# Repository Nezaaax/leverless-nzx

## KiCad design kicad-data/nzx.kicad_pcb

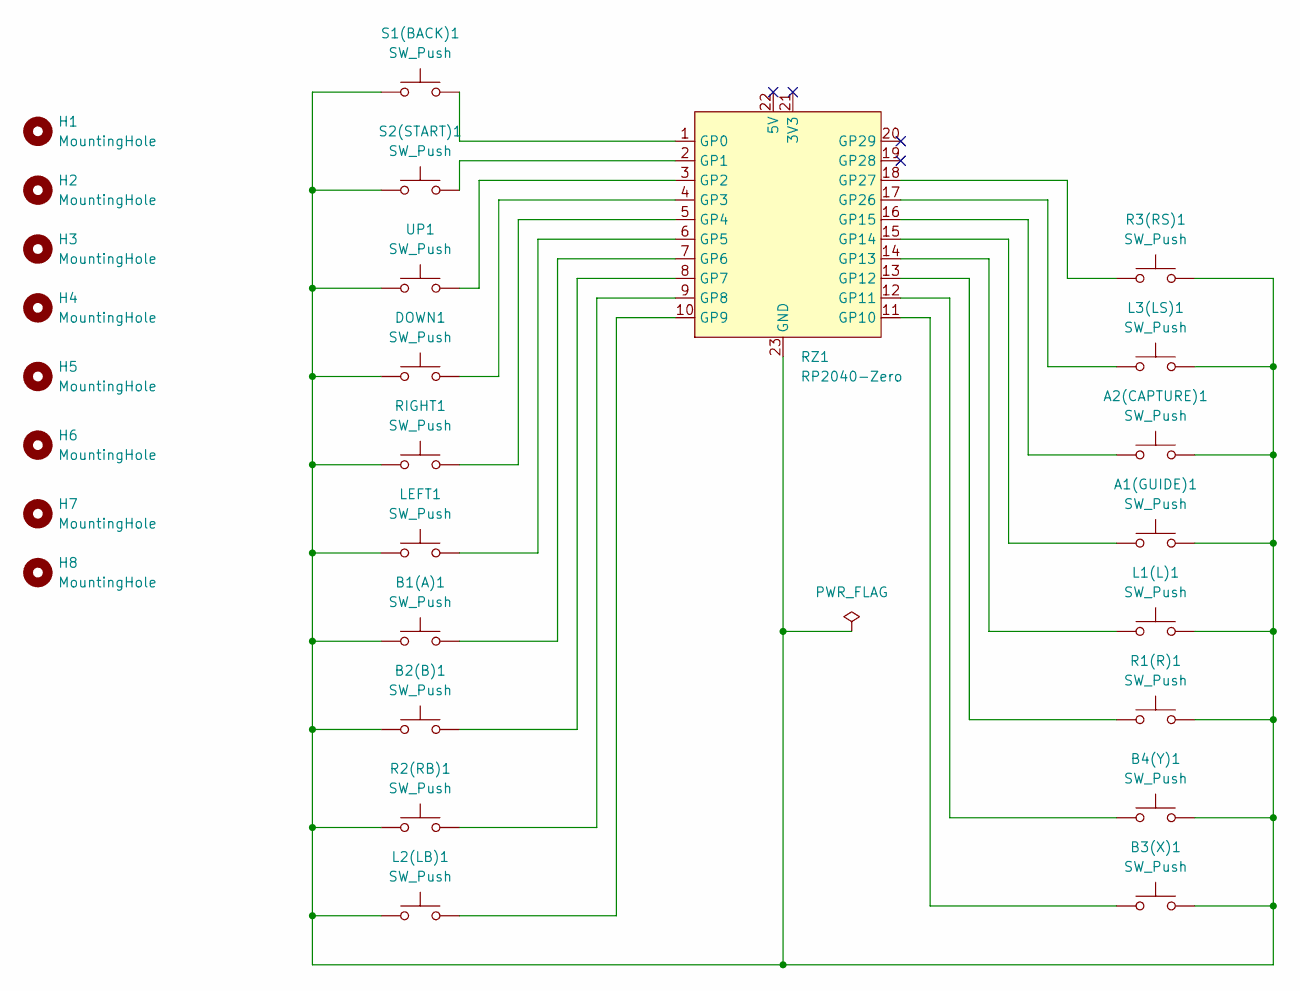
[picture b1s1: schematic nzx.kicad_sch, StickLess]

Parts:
A1(GUIDE)1, A2(CAPTURE)1: SW_Push; Kailh_Choc_V2
B1(A)1, B2(B)1, B3(X)1, B4(Y)1: SW_Push; Kailh_Choc_V2_24
DOWN1: SW_Push; Kailh_Choc_V2_24
H1, H2, H3, H4, H5, H6, H7, H8: MountingHole; MountingHole_6mm
L1(L)1, L2(LB)1, L3(LS)1: SW_Push; Kailh_Choc_V2_24
LEFT1: SW_Push; Kailh_Choc_V2_24
R1(R)1, R2(RB)1, R3(RS)1: SW_Push; Kailh_Choc_V2_24
RIGHT1: SW_Push; Kailh_Choc_V2_24
RZ1: RP2040-Zero
S1(BACK)1: SW_Push; Kailh_Choc_V2_24
S2(START)1: SW_Push; Kailh_Choc_V2
UP1: SW_Push; Kailh_Choc_V2_30

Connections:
unnamed: A1(GUIDE)1.2, A2(CAPTURE)1.2, B1(A)1.1, B2(B)1.1, B3(X)1.2, B4(Y)1.2, DOWN1.1, L1(L)1.2, L2(LB)1.1, L3(LS)1.2, LEFT1.1, R1(R)1.2, R2(RB)1.1, R3(RS)1.2, RIGHT1.1, RZ1.23 (GND), S1(BACK)1.1, S2(START)1.1, UP1.1
unnamed: RZ1.1 (GP0), S1(BACK)1.2
unnamed: RZ1.2 (GP1), S2(START)1.2
unnamed: RZ1.3 (GP2), UP1.2
unnamed: DOWN1.2, RZ1.4 (GP3)
unnamed: RIGHT1.2, RZ1.5 (GP4)
unnamed: LEFT1.2, RZ1.6 (GP5)
unnamed: B1(A)1.2, RZ1.7 (GP6)
unnamed: B2(B)1.2, RZ1.8 (GP7)
unnamed: R2(RB)1.2, RZ1.9 (GP8)
unnamed: L2(LB)1.2, RZ1.10 (GP9)
unnamed: B3(X)1.1, RZ1.11 (GP10)
unnamed: B4(Y)1.1, RZ1.12 (GP11)
unnamed: R1(R)1.1, RZ1.13 (GP12)
unnamed: L1(L)1.1, RZ1.14 (GP13)
unnamed: A1(GUIDE)1.1, RZ1.15 (GP14)
unnamed: A2(CAPTURE)1.1, RZ1.16 (GP15)
unnamed: L3(LS)1.1, RZ1.17 (GP26)
unnamed: R3(RS)1.1, RZ1.18 (GP27)

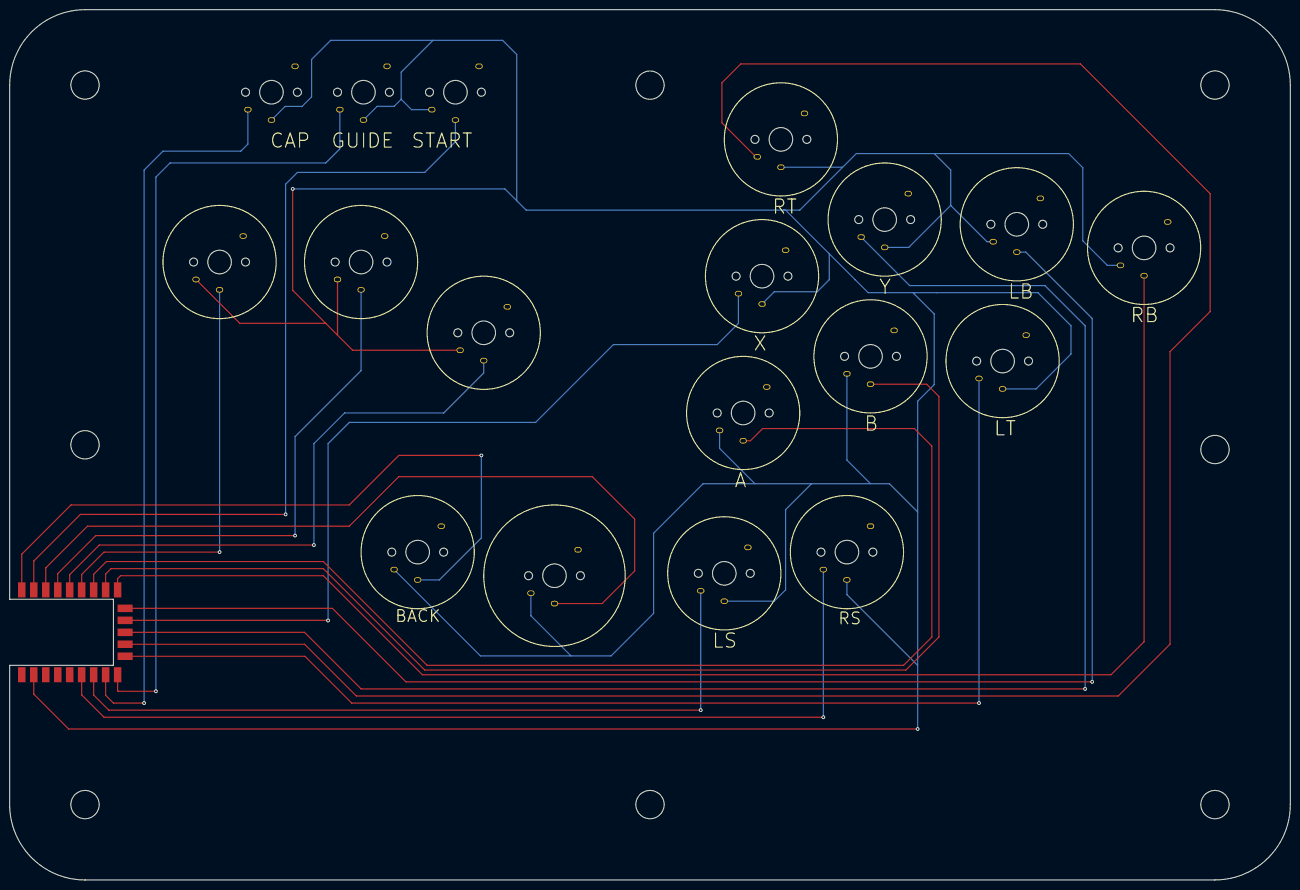
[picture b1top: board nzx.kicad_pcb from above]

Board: 2 copper layers, 271.5 x 184.5 mm, 27 parts (0 on the bottom side), 19 nets.

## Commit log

2024-08-26 Add completed data set for division1
2024-08-31 fix: Update button wiring and adjust edge data
2024-09-15 feat - Added revision2
2024-09-15 chore - Refactored directory
2024-09-15 chore - Edit md
